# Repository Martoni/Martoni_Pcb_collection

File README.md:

Collection of PCB made with Kicad

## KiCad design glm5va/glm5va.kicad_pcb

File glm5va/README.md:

# GateMate 5V Adapt 
 
Little PCB to adapt 2.5v GateMate signals to 5V for matrix Led.

Adapt board for Olimex [GatemateA1-EVB board](https://www.olimex.com/Products/FPGA/GateMate/GateMateA1-EVB/open-source-hardware).

## Gerber

Tutorial to make gerber : https://jlcpcb.com/help/article/how-to-generate-gerber-and-drill-files-in-kicad-8

## Ressources

- [Hub75 with tangnano](https://learn.lushaylabs.com/led-panel-hub75/)

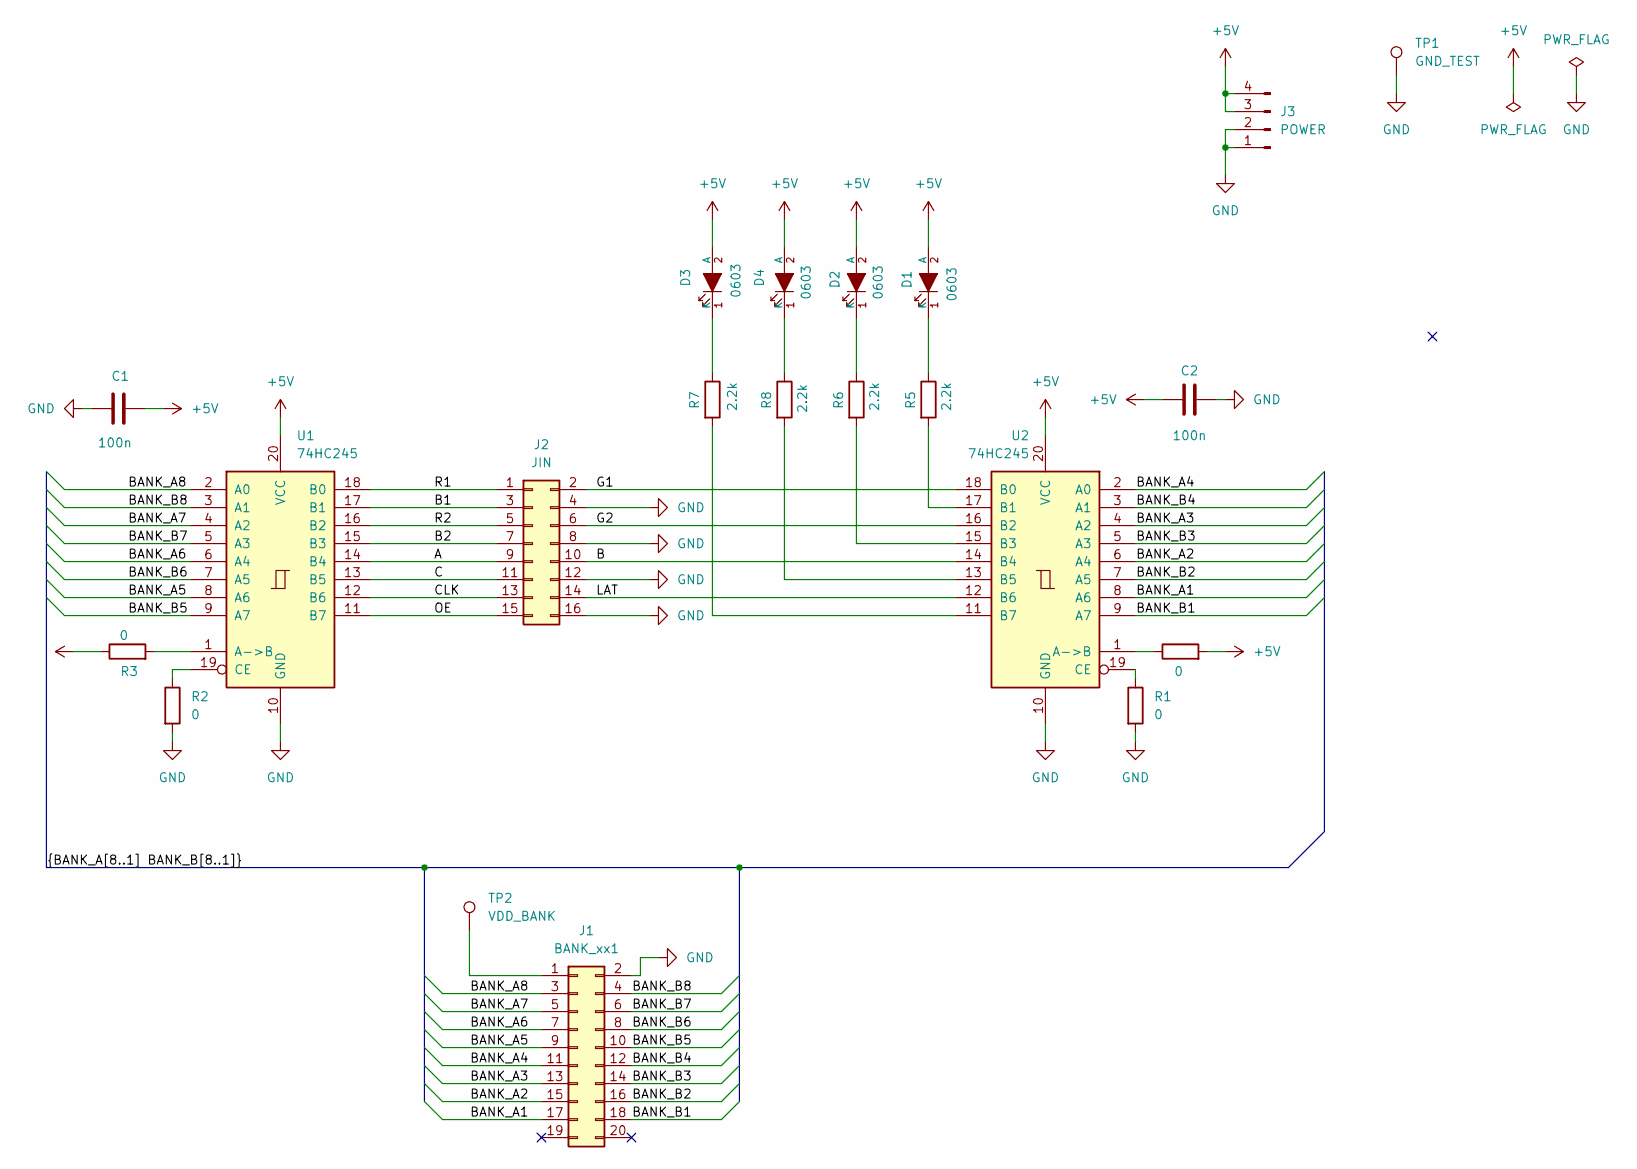
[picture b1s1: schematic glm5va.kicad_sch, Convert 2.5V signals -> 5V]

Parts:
C1, C2: 100n; C_0603_1608Metric
D1, D2, D3, D4: 0603; LED_1206_3216Metric
J1: BANK_xx1; PinHeader_2x10_P2.54mm_Vertical
J2: JIN; IDC-Header_2x08_P2.54mm_Vertical
J3: POWER; Molex_KK-396_A-41791-0004_1x04_P3.96mm_Vertical
R1, R2, R3, R4: 0; R_0603_1608Metric
R5, R6, R7, R8: 2.2k; R_0603_1608Metric
TP1: GND_TEST; Pin_D1.0mm_L10.0mm
TP2: VDD_BANK; Pin_D1.0mm_L10.0mm
U1, U2: 74HC245; TSSOP-20_4.4x6.5mm_P0.65mm

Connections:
/A: J2.9, U1.14 (B4)
/B: J2.10, U2.14 (B4)
/B1: J2.3, U1.17 (B1)
/B2: J2.7, U1.15 (B3)
/BANK_A1: J1.17, U2.8 (A6)
/BANK_A2: J1.15, U2.6 (A4)
/BANK_A3: J1.13, U2.4 (A2)
/BANK_A4: J1.11, U2.2 (A0)
/BANK_A5: J1.9, U1.8 (A6)
/BANK_A6: J1.7, U1.6 (A4)
/BANK_A7: J1.5, U1.4 (A2)
/BANK_A8: J1.3, U1.2 (A0)
/BANK_B1: J1.18, U2.9 (A7)
/BANK_B2: J1.16, U2.7 (A5)
/BANK_B3: J1.14, U2.5 (A3)
/BANK_B4: J1.12, U2.3 (A1)
/BANK_B5: J1.10, U1.9 (A7)
/BANK_B6: J1.8, U1.7 (A5)
/BANK_B7: J1.6, U1.5 (A3)
/BANK_B8: J1.4, U1.3 (A1)
/C: J2.11, U1.13 (B5)
/CLK: J2.13, U1.12 (B6)
/G1: J2.2, U2.18 (B0)
/G2: J2.6, U2.16 (B2)
/LAT: J2.14, U2.12 (B6)
/OE: J2.15, U1.11 (B7)
/R1: J2.1, U1.18 (B0)
/R2: J2.5, U1.16 (B2)
unnamed: D1.1 (K), R5.1
unnamed: D2.1 (K), R6.1
unnamed: D3.1 (K), R7.1
unnamed: D4.1 (K), R8.1
unnamed: J1.1, TP2.1
unnamed: R3.2, U1.1 (A->B)
unnamed: R2.1, U1.19 (CE)
unnamed: R4.1, U2.1 (A->B)
unnamed: R5.2, U2.17 (B1)
unnamed: R6.2, U2.15 (B3)
unnamed: R8.2, U2.13 (B5)
unnamed: R7.2, U2.11 (B7)
unnamed: R1.1, U2.19 (CE)

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
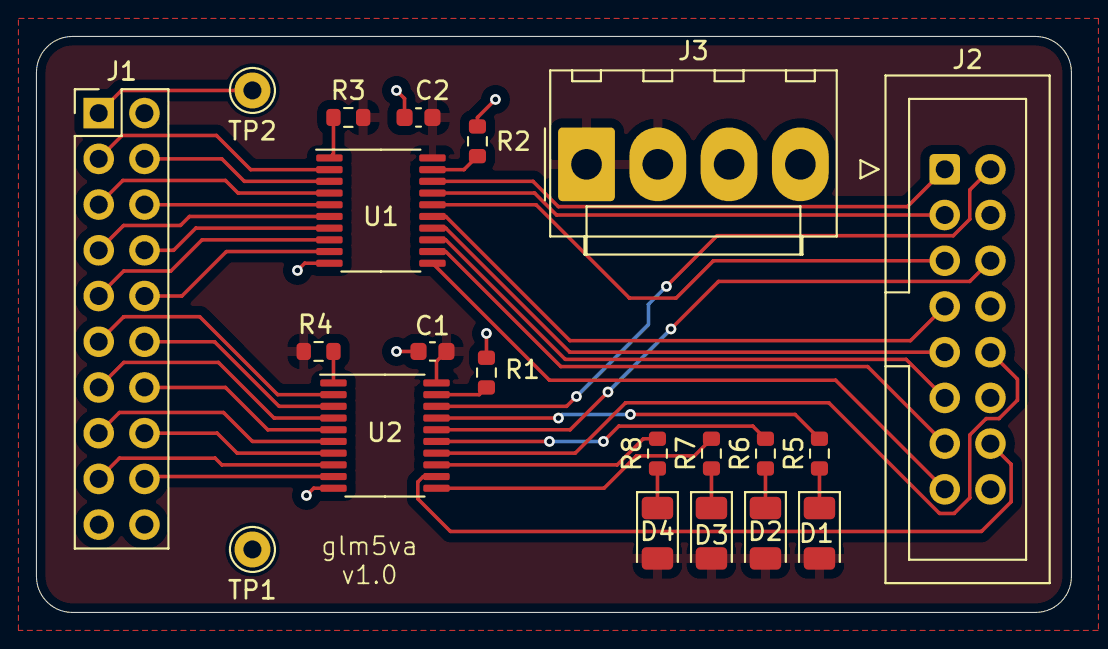
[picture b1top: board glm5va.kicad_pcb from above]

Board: 2 copper layers, 57.5 x 32.0 mm, 21 parts (0 on the bottom side), 43 nets.

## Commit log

2025-01-20 adding 2.5v to 5v board adapt schematic for GatemateA1_EVB
2025-01-20 adding pdf for schematic
2025-01-21 GbSwitchFp
2025-01-21 glm5va: footprint association
2025-01-22 glm5va: place components
2025-01-23 glm5va: routing and layers ok
2025-01-23 glm5va: jlcpcb fabrication files
2025-02-19 glm5va: update pdf-schematic, add 3D view
2025-02-19 glm5va: adding images
2025-02-26 glm5va: pattern test boilerplate rtl
2025-02-27 GbSwitchFp: adding 3D view and schematic pdf
2025-03-01 trying to blink leds
2025-03-04 trying hub75 tangnano tutorial
2025-03-05 glm5va: simple four leds blinker
2025-03-08 glm5va: rtl test
2025-03-09 trying chat gpt, doesn't work
2025-03-15 vectorize ports
